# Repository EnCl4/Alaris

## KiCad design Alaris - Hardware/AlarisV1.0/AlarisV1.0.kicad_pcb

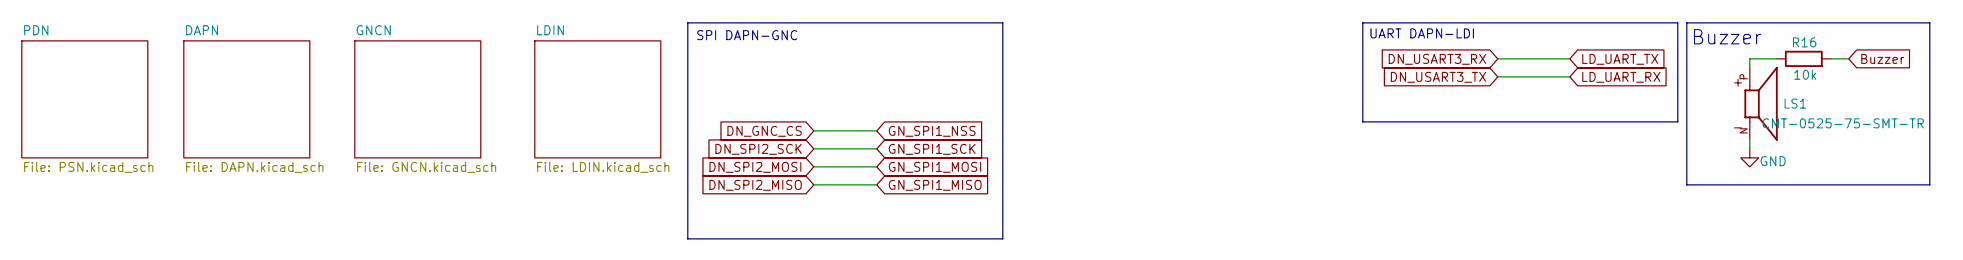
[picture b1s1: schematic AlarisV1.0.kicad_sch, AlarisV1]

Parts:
LS1: CMT-0525-75-SMT-TR; Buzzer5mm; PARTREV 1.0
R16: 10k; R_0603_1608Metric_Pad0.98x0.95mm_HandSolder

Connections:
Buzzer: R16.2; also elsewhere on the board
GND: LS1.N; also elsewhere on the board
unnamed: LS1.P, R16.1

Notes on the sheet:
Buzzer
SPI DAPN-GNC
UART DAPN-LDI

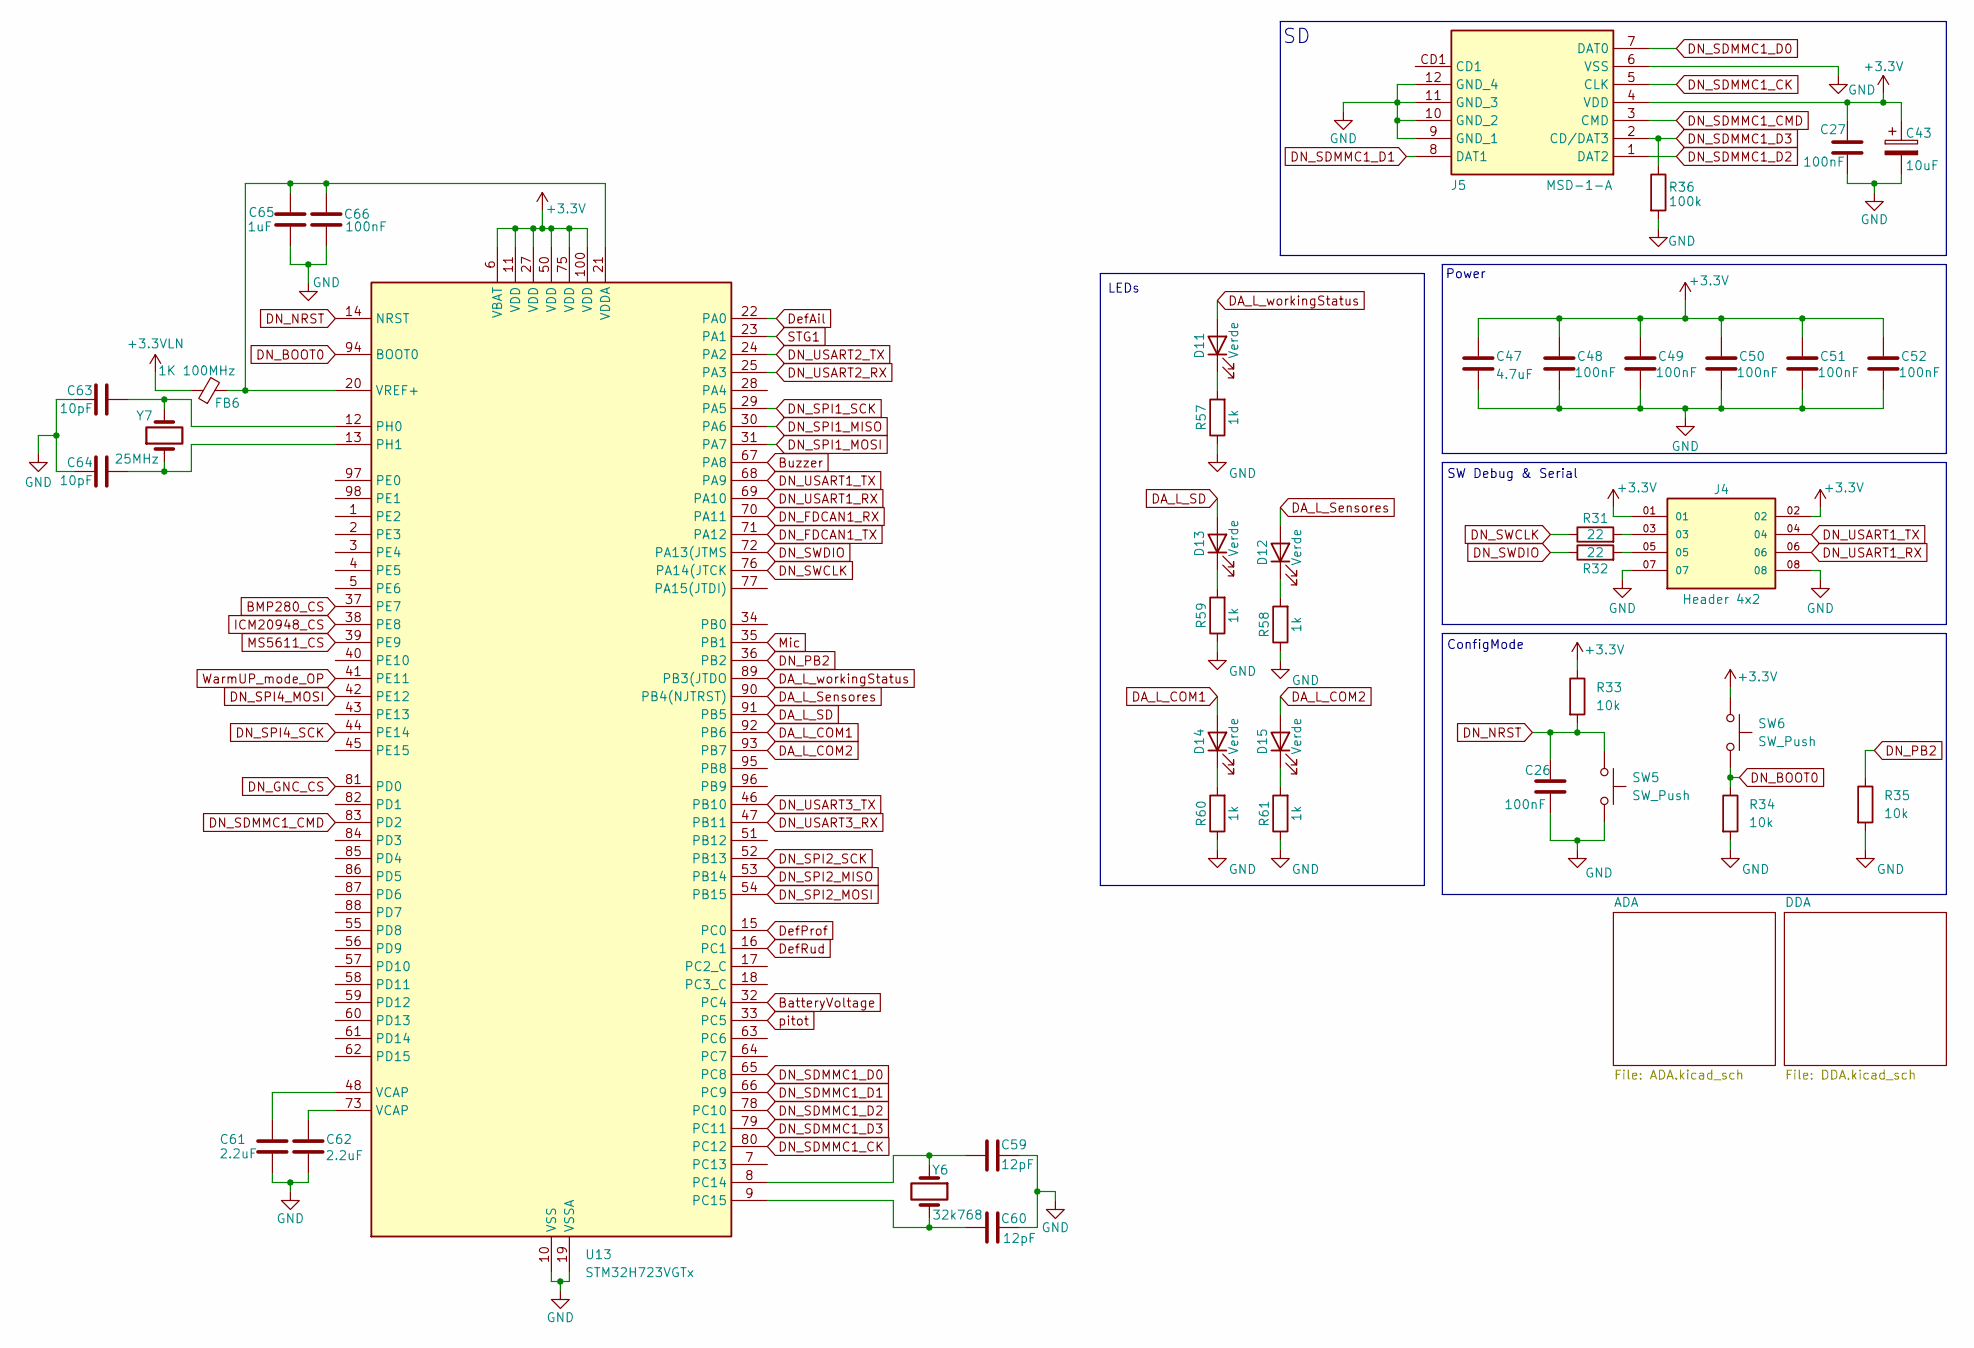
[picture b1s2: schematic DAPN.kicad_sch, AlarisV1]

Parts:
C26, C27, C48, C49, C50, C51, C52, C66: 100nF; C_0603_1608Metric_Pad1.08x0.95mm_HandSolder
C43: 10uF; CP_EIA-3216-18_Kemet-A_Pad1.58x1.35mm_HandSolder
C47: 4.7uF; C_0603_1608Metric_Pad1.08x0.95mm_HandSolder
C59, C60: 12pF; C_0603_1608Metric_Pad1.08x0.95mm_HandSolder
C61, C62: 2.2uF; C_0603_1608Metric_Pad1.08x0.95mm_HandSolder
C63, C64: 10pF; C_0603_1608Metric_Pad1.08x0.95mm_HandSolder
C65: 1uF; C_0603_1608Metric_Pad1.08x0.95mm_HandSolder
D11, D12, D13, D14, D15: Verde; LED_0603_1608Metric_Pad1.05x0.95mm_HandSolder
FB6: 1K 100MHz; C_0603_1608Metric_Pad1.08x0.95mm_HandSolder
J4: Header 4x2; Header4x2; PARTREV R
J5: MSD-1-A; MSD1A; Mouser Part Number 179-MSD-1-A
R31, R32: 22; R_0603_1608Metric_Pad0.98x0.95mm_HandSolder
R33, R34, R35: 10k; R_0603_1608Metric_Pad0.98x0.95mm_HandSolder
R36: 100k; R_0603_1608Metric_Pad0.98x0.95mm_HandSolder
R57, R58, R59, R60, R61: 1k; R_0603_1608Metric_Pad0.98x0.95mm_HandSolder
SW5, SW6: SW_Push; SKRK
U13: STM32H723VGTx; LQFP-100_14x14mm_P0.5mm
Y6: 32k768; Crystal_SMD_3215-2Pin_3.2x1.5mm
Y7: 25MHz; Crystal_SMD_3225-4Pin_3.2x2.5mm

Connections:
+3.3V: C27.1, C43.1, C47.1, C48.1, C49.1, C50.1, C51.1, C52.1, J4.01, J4.02, J5.4 (VDD), R33.1, SW6.1, U13.6 (VBAT), U13.11 (VDD), U13.27 (VDD), U13.50 (VDD), U13.75 (VDD), U13.100 (VDD); also elsewhere on the board
+3.3VLN: FB6.1; also elsewhere on the board
BMP280_CS: U13.37 (PE7); also elsewhere on the board
BatteryVoltage: U13.32 (PC4); also elsewhere on the board
Buzzer: U13.67 (PA8); also elsewhere on the board
DA_L_COM1: D14.2 (A), U13.92 (PB6)
DA_L_COM2: D15.2 (A), U13.93 (PB7)
DA_L_SD: D13.2 (A), U13.91 (PB5)
DA_L_Sensores: D12.2 (A), U13.90 (PB4(NJTRST))
DA_L_workingStatus: D11.2 (A), U13.89 (PB3(JTDO)
DN_BOOT0: R34.1, SW6.2, U13.94 (BOOT0)
DN_FDCAN1_RX: U13.70 (PA11)
DN_FDCAN1_TX: U13.71 (PA12)
DN_NRST: C26.2, R33.2, SW5.1, U13.14 (NRST)
DN_PB2: R35.1, U13.36 (PB2)
DN_SDMMC1_CK: J5.5 (CLK), U13.80 (PC12)
DN_SDMMC1_CMD: J5.3 (CMD), U13.83 (PD2)
DN_SDMMC1_D0: J5.7 (DAT0), U13.65 (PC8)
DN_SDMMC1_D1: J5.8 (DAT1), U13.66 (PC9)
DN_SDMMC1_D2: J5.1 (DAT2), U13.78 (PC10)
DN_SDMMC1_D3: J5.2 (CD/DAT3), R36.1, U13.79 (PC11)
DN_SPI1_MISO: U13.30 (PA6); also elsewhere on the board
DN_SPI1_MOSI: U13.31 (PA7); also elsewhere on the board
DN_SPI1_SCK: U13.29 (PA5); also elsewhere on the board
DN_SPI4_MOSI: U13.42 (PE12)
DN_SPI4_SCK: U13.44 (PE14)
DN_SWCLK: R31.1, U13.76 (PA14(JTCK)
DN_SWDIO: R32.1, U13.72 (PA13(JTMS)
DN_USART1_RX: J4.06, U13.69 (PA10)
DN_USART1_TX: J4.04, U13.68 (PA9)
DN_USART2_RX: U13.25 (PA3); also elsewhere on the board
DN_USART2_TX: U13.24 (PA2); also elsewhere on the board
DefAil: U13.22 (PA0); also elsewhere on the board
DefProf: U13.15 (PC0); also elsewhere on the board
DefRud: U13.16 (PC1); also elsewhere on the board
GND: C26.1, C27.2, C43.2, C47.2, C48.2, C49.2, C50.2, C51.2, C52.2, C59.2, C60.2, C61.2, C62.2, C63.2, C64.2, C65.2, C66.2, J4.07, J4.08, J5.6 (VSS), J5.9 (GND_1), J5.10 (GND_2), J5.11 (GND_3), J5.12 (GND_4), R34.2, R35.2, R36.2, R57.1, R58.1, R59.1, R60.1, R61.1, SW5.2, U13.10 (VSS), U13.19 (VSSA), U13.26 (VSS), U13.49 (VSS), U13.74 (VSS), U13.99 (VSS); also elsewhere on the board
ICM20948_CS: U13.38 (PE8); also elsewhere on the board
MS5611_CS: U13.39 (PE9); also elsewhere on the board
Mic: U13.35 (PB1); also elsewhere on the board
unnamed: C61.1, U13.48 (VCAP)
unnamed: C62.1, U13.73 (VCAP)
unnamed: D11.1 (K), R57.2
unnamed: D12.1 (K), R58.2
unnamed: D13.1 (K), R59.2
unnamed: D14.1 (K), R60.2
unnamed: D15.1 (K), R61.2
unnamed: J4.03, R31.2
unnamed: J4.05, R32.2
unnamed: C59.1, U13.8 (PC14), Y6.1
unnamed: C60.1, U13.9 (PC15), Y6.2
unnamed: C63.1, U13.12 (PH0), Y7.2
unnamed: C64.1, U13.13 (PH1), Y7.1
unnamed: C65.1, C66.1, FB6.2, U13.20 (VREF+), U13.21 (VDDA)
STG1: U13.23 (PA1); also elsewhere on the board
WarmUP_mode_OP: U13.41 (PE11); also elsewhere on the board
pitot: U13.33 (PC5); also elsewhere on the board

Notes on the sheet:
ConfigMode
LEDs
Power
SW Debug & Serial

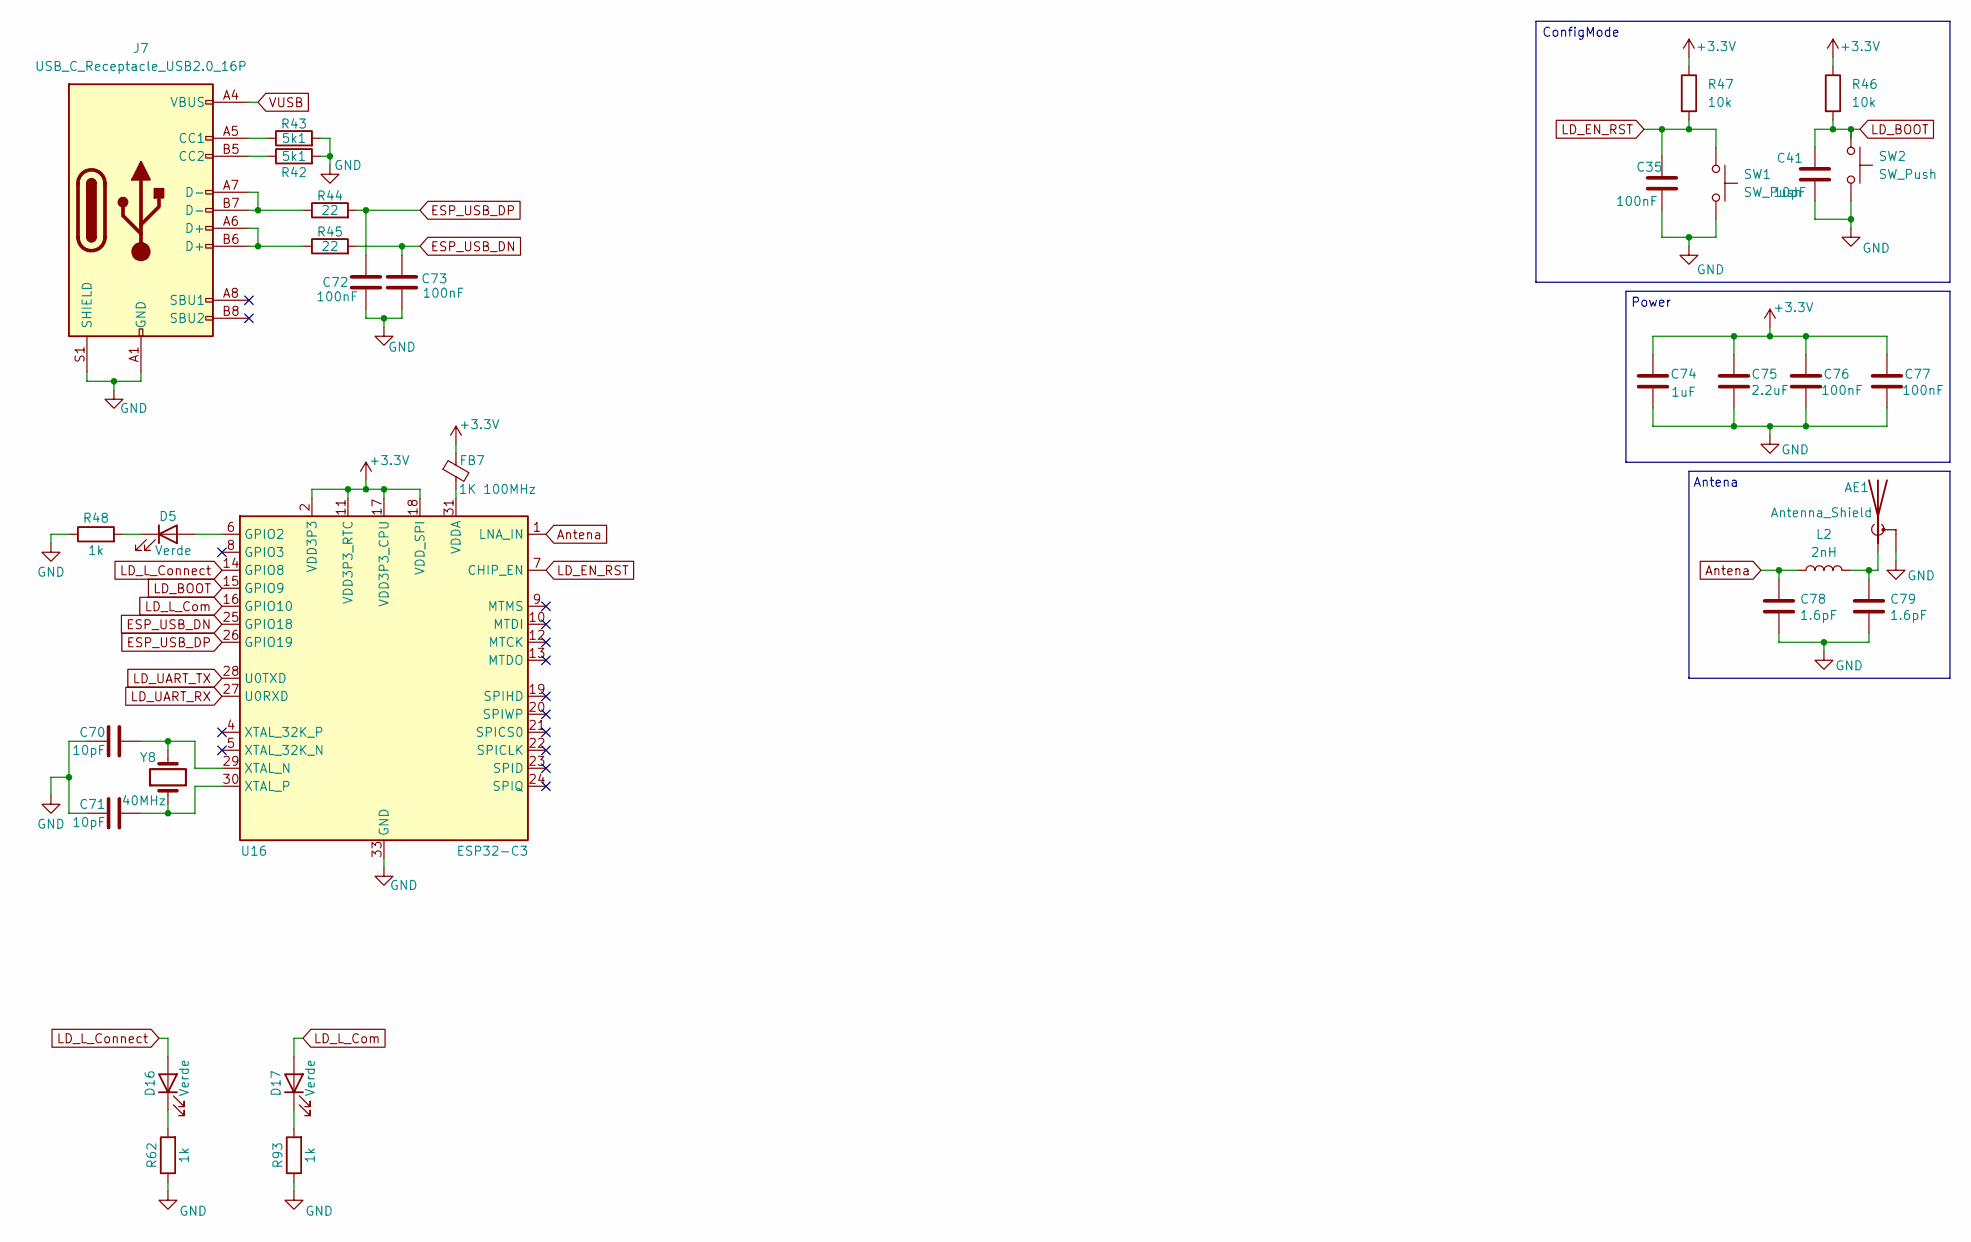
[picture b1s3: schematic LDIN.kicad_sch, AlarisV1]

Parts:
AE1: Antenna_Shield
C35, C72, C73, C76, C77: 100nF; C_0603_1608Metric_Pad1.08x0.95mm_HandSolder
C41, C70, C71: 10pF; C_0603_1608Metric_Pad1.08x0.95mm_HandSolder
C74: 1uF; C_0603_1608Metric_Pad1.08x0.95mm_HandSolder
C75: 2.2uF; C_0603_1608Metric_Pad1.08x0.95mm_HandSolder
C78, C79: 1.6pF; C_0603_1608Metric_Pad1.08x0.95mm_HandSolder
D5, D16, D17: Verde; LED_0603_1608Metric_Pad1.05x0.95mm_HandSolder
FB7: 1K 100MHz; C_0603_1608Metric_Pad1.08x0.95mm_HandSolder
J7: USB_C_Receptacle_USB2.0_16P; USB_C_Receptacle_G-Switch_GT-USB-7010ASV
L2: 2nH; L_0603_1608Metric_Pad1.05x0.95mm_HandSolder
R42, R43: 5k1; R_0603_1608Metric_Pad0.98x0.95mm_HandSolder
R44, R45: 22; R_0603_1608Metric_Pad0.98x0.95mm_HandSolder
R46, R47: 10k; R_0603_1608Metric_Pad0.98x0.95mm_HandSolder
R48, R62, R93: 1k; R_0603_1608Metric_Pad0.98x0.95mm_HandSolder
SW1, SW2: SW_Push; SKRK
U16: ESP32-C3; QFN-32-1EP_5x5mm_P0.5mm_EP3.7x3.7mm
Y8: 40MHz; Crystal_SMD_3225-4Pin_3.2x2.5mm

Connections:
+3.3V: C74.1, C75.1, C76.1, C77.1, FB7.1, R46.1, R47.1, U16.2 (VDD3P3), U16.3 (VDD3P3), U16.11 (VDD3P3_RTC), U16.17 (VDD3P3_CPU), U16.18 (VDD_SPI); also elsewhere on the board
Antena: C78.1, L2.1, U16.1 (LNA_IN)
ESP_USB_DN: C73.1, R45.2, U16.25 (GPIO18)
ESP_USB_DP: C72.1, R44.2, U16.26 (GPIO19)
GND: AE1.2 (Shield), C35.1, C41.1, C70.2, C71.2, C72.2, C73.2, C74.2, C75.2, C76.2, C77.2, C78.2, C79.2, J7.A1 (GND), J7.A12 (GND), J7.B1 (GND), J7.B12 (GND), J7.S1 (SHIELD), R42.2, R43.2, R48.1, R62.1, R93.1, SW1.2, SW2.2, U16.33 (GND); also elsewhere on the board
LD_BOOT: C41.2, R46.2, SW2.1, U16.15 (GPIO9)
LD_EN_RST: C35.2, R47.2, SW1.1, U16.7 (CHIP_EN)
LD_L_Com: D17.2 (A), U16.16 (GPIO10)
LD_L_Connect: D16.2 (A), U16.14 (GPIO8)
unnamed: AE1.1 (A), C79.1, L2.2
unnamed: D5.2 (A), U16.6 (GPIO2)
unnamed: D5.1 (K), R48.2
unnamed: D16.1 (K), R62.2
unnamed: D17.1 (K), R93.2
unnamed: FB7.2, U16.31 (VDDA), U16.32 (VDDA)
unnamed: J7.A5 (CC1), R43.1
unnamed: J7.B5 (CC2), R42.1
unnamed: J7.A6 (D+), J7.B6 (D+), R45.1
unnamed: J7.A7 (D-), J7.B7 (D-), R44.1
unnamed: C70.1, U16.29 (XTAL_N), Y8.2
unnamed: C71.1, U16.30 (XTAL_P), Y8.1
VUSB: J7.A4 (VBUS), J7.A9 (VBUS), J7.B4 (VBUS), J7.B9 (VBUS)

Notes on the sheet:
Power
Antena
ConfigMode

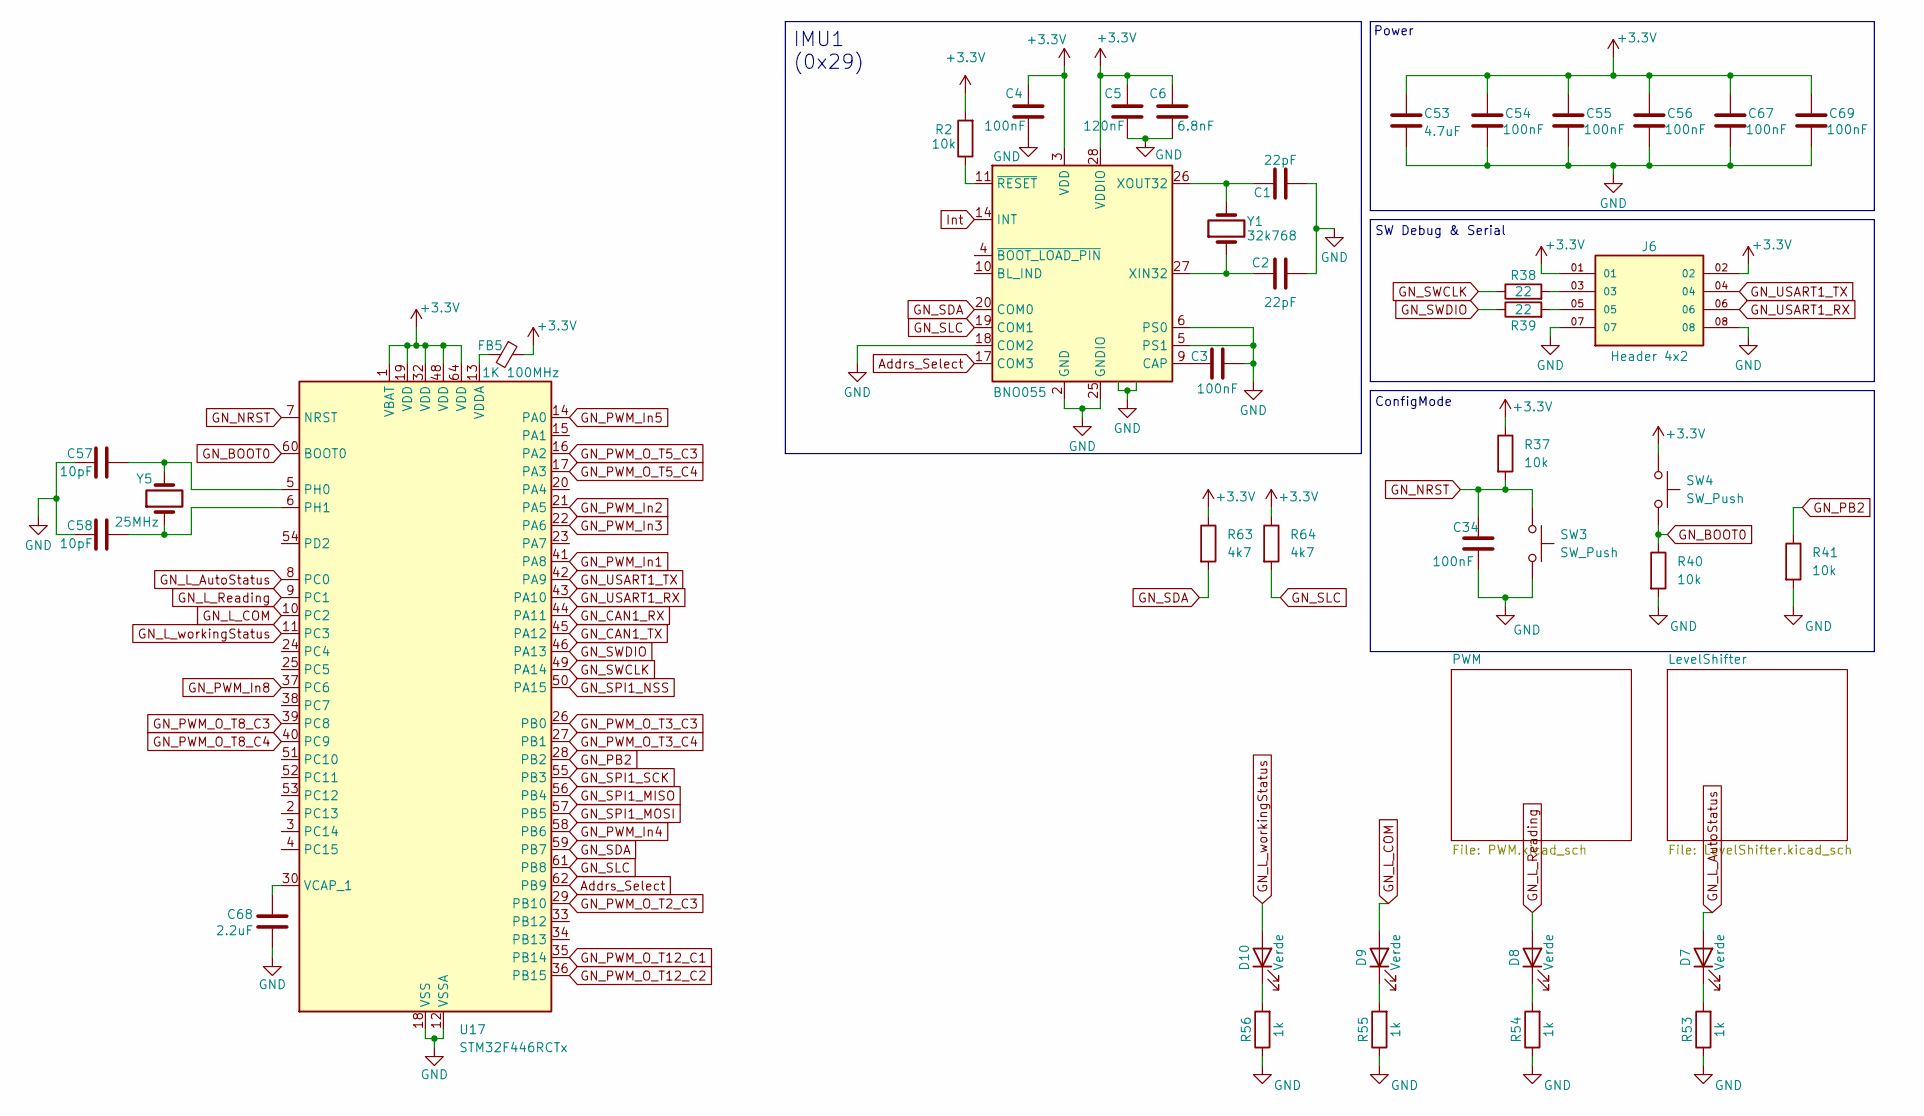
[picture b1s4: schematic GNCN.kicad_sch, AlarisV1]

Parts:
C1, C2: 22pF; C_0603_1608Metric_Pad1.08x0.95mm_HandSolder
C3, C4, C34, C54, C55, C56, C67, C69: 100nF; C_0603_1608Metric_Pad1.08x0.95mm_HandSolder
C5: 120nF; C_0603_1608Metric_Pad1.08x0.95mm_HandSolder
C6: 6.8nF; C_0603_1608Metric_Pad1.08x0.95mm_HandSolder
C53: 4.7uF; C_0603_1608Metric_Pad1.08x0.95mm_HandSolder
C57, C58: 10pF; C_0603_1608Metric_Pad1.08x0.95mm_HandSolder
C68: 2.2uF; C_0603_1608Metric_Pad1.08x0.95mm_HandSolder
D7, D8, D9, D10: Verde; LED_0603_1608Metric_Pad1.05x0.95mm_HandSolder
FB5: 1K 100MHz; C_0603_1608Metric_Pad1.08x0.95mm_HandSolder
J6: Header 4x2; Header4x2; PARTREV R
R2, R37, R40, R41: 10k; R_0603_1608Metric_Pad0.98x0.95mm_HandSolder
R38, R39: 22; R_0603_1608Metric_Pad0.98x0.95mm_HandSolder
R53, R54, R55, R56: 1k; R_0603_1608Metric_Pad0.98x0.95mm_HandSolder
R63, R64: 4k7; R_0603_1608Metric_Pad0.98x0.95mm_HandSolder
SW3, SW4: SW_Push; SKRK
U2: BNO055; LGA-28_5.2x3.8mm_P0.5mm
U17: STM32F446RCTx; LQFP-64_10x10mm_P0.5mm
Y1: 32k768; Crystal_SMD_3215-2Pin_3.2x1.5mm
Y5: 25MHz; Crystal_SMD_3225-4Pin_3.2x2.5mm

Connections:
+3.3V: C4.1, C5.1, C6.1, C53.1, C54.1, C55.1, C56.1, C67.1, C69.1, FB5.1, J6.01, J6.02, R2.2, R37.1, R63.1, R64.1, SW4.1, U2.3 (VDD), U2.28 (VDDIO), U17.1 (VBAT), U17.19 (VDD), U17.32 (VDD), U17.48 (VDD), U17.64 (VDD); also elsewhere on the board
Addrs_Select: U2.17 (COM3), U17.62 (PB9)
GND: C1.2, C2.2, C3.2, C4.2, C5.2, C6.2, C34.1, C53.2, C54.2, C55.2, C56.2, C57.2, C58.2, C67.2, C68.2, C69.2, J6.07, J6.08, R40.2, R41.2, R53.1, R54.1, R55.1, R56.1, SW3.2, U2.2 (GND), U2.5 (PS1), U2.6 (PS0), U2.15 (PIN15), U2.16 (PIN16), U2.18 (COM2), U2.25 (GNDIO), U17.12 (VSSA), U17.18 (VSS), U17.31 (VSS), U17.47 (VSS), U17.63 (VSS); also elsewhere on the board
GN_BOOT0: R40.1, SW4.2, U17.60 (BOOT0)
GN_CAN1_RX: U17.44 (PA11)
GN_CAN1_TX: U17.45 (PA12)
GN_L_AutoStatus: D7.2 (A), U17.8 (PC0)
GN_L_COM: D9.2 (A), U17.10 (PC2)
GN_L_Reading: D8.2 (A), U17.9 (PC1)
GN_L_workingStatus: D10.2 (A), U17.11 (PC3)
GN_NRST: C34.2, R37.2, SW3.1, U17.7 (NRST)
GN_PB2: R41.1, U17.28 (PB2)
GN_PWM_In1: U17.41 (PA8); also elsewhere on the board
GN_PWM_In2: U17.21 (PA5); also elsewhere on the board
GN_PWM_In3: U17.22 (PA6); also elsewhere on the board
GN_PWM_In4: U17.58 (PB6); also elsewhere on the board
GN_PWM_In5: U17.14 (PA0); also elsewhere on the board
GN_PWM_In8: U17.37 (PC6); also elsewhere on the board
GN_PWM_O_T2_C3: U17.29 (PB10); also elsewhere on the board
GN_PWM_O_T3_C3: U17.26 (PB0); also elsewhere on the board
GN_PWM_O_T3_C4: U17.27 (PB1); also elsewhere on the board
GN_PWM_O_T5_C3: U17.16 (PA2)
GN_PWM_O_T5_C4: U17.17 (PA3); also elsewhere on the board
GN_PWM_O_T8_C3: U17.39 (PC8); also elsewhere on the board
GN_PWM_O_T8_C4: U17.40 (PC9); also elsewhere on the board
GN_PWM_O_T12_C1: U17.35 (PB14); also elsewhere on the board
GN_PWM_O_T12_C2: U17.36 (PB15); also elsewhere on the board
GN_SDA: R63.2, U2.20 (COM0), U17.59 (PB7)
GN_SLC: R64.2, U2.19 (COM1), U17.61 (PB8)
GN_SWCLK: R38.1, U17.49 (PA14)
GN_SWDIO: R39.1, U17.46 (PA13)
GN_USART1_RX: J6.06, U17.43 (PA10)
GN_USART1_TX: J6.04, U17.42 (PA9)
Int: U2.14 (INT)
unnamed: D7.1 (K), R53.2
unnamed: D8.1 (K), R54.2
unnamed: D9.1 (K), R55.2
unnamed: D10.1 (K), R56.2
unnamed: J6.03, R38.2
unnamed: J6.05, R39.2
unnamed: C3.1, U2.9 (CAP)
unnamed: C2.1, U2.27 (XIN32), Y1.1
unnamed: C1.1, U2.26 (XOUT32), Y1.2
unnamed: R2.1, U2.11 (~RESET)
unnamed: C57.1, U17.5 (PH0), Y5.2
unnamed: C58.1, U17.6 (PH1), Y5.1
unnamed: C68.1, U17.30 (VCAP_1)
unnamed: FB5.2, U17.13 (VDDA)

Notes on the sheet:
SW Debug & Serial
Power
ConfigMode
IMU1 (0x29)

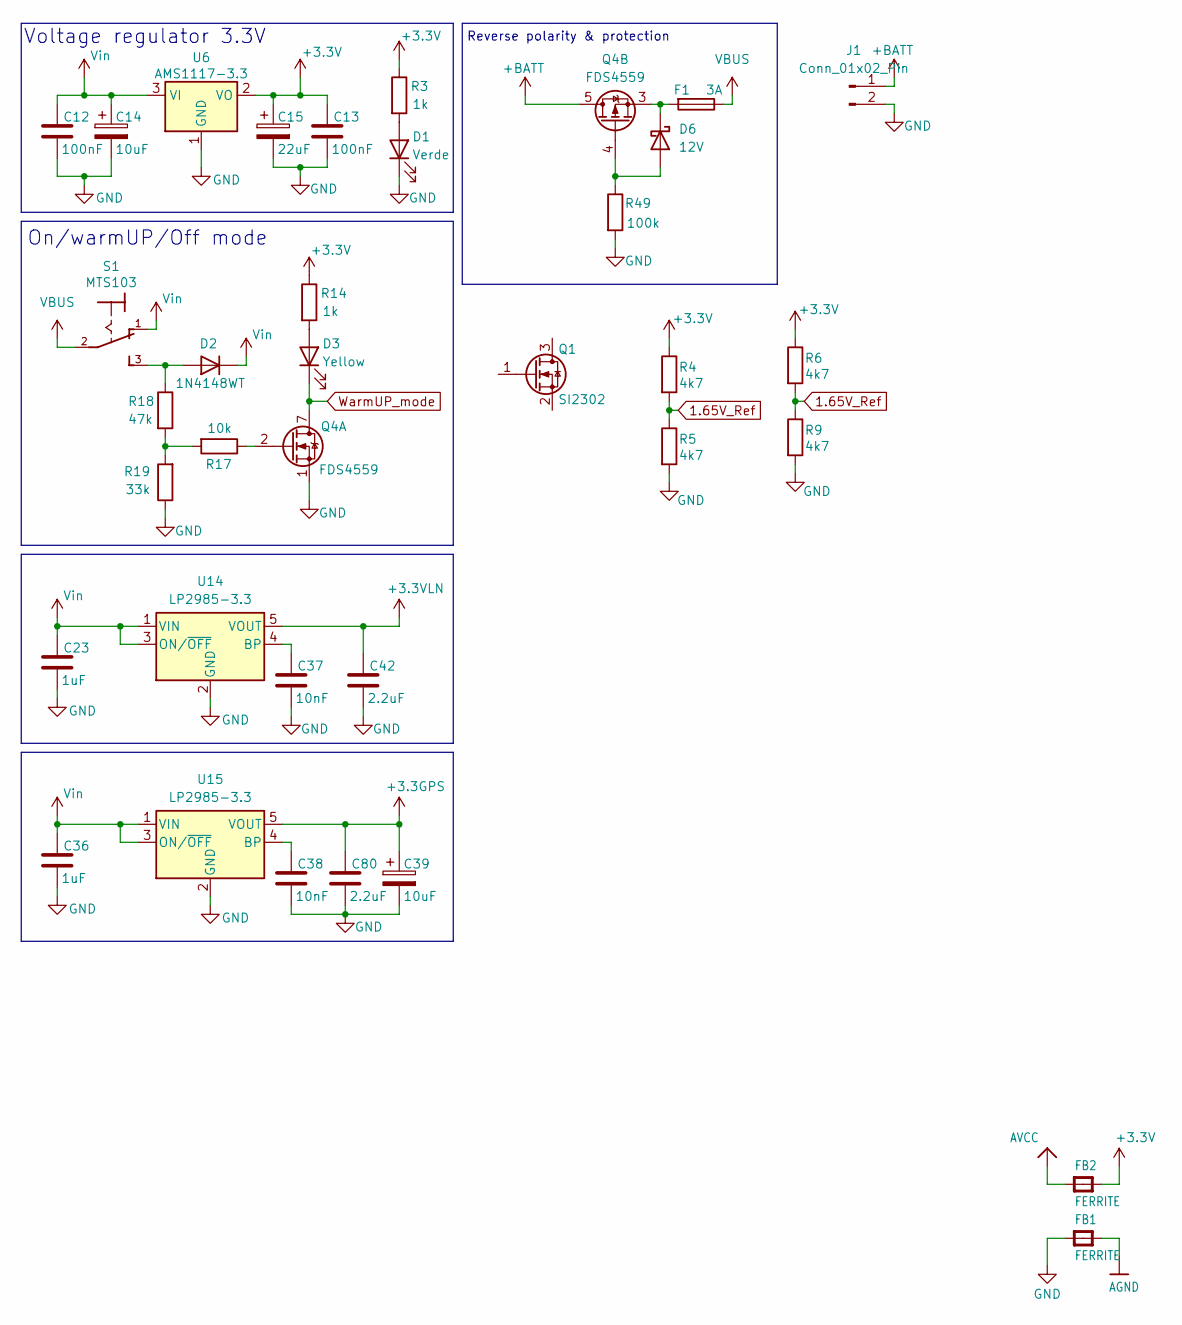
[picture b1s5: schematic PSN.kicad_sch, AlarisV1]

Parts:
C12, C13: 100nF; C_0603_1608Metric_Pad1.08x0.95mm_HandSolder
C14, C39: 10uF; CP_EIA-3216-18_Kemet-A_Pad1.58x1.35mm_HandSolder
C15: 22uF; CP_EIA-3216-18_Kemet-A_Pad1.58x1.35mm_HandSolder
C23, C36: 1uF; C_0603_1608Metric_Pad1.08x0.95mm_HandSolder
C37, C38: 10nF; C_0603_1608Metric_Pad1.08x0.95mm_HandSolder
C42, C80: 2.2uF; C_0603_1608Metric_Pad1.08x0.95mm_HandSolder
D1: Verde; LED_0603_1608Metric_Pad1.05x0.95mm_HandSolder
D2: 1N4148WT; D_SOD-523
D3: Yellow; LED_0603_1608Metric_Pad1.05x0.95mm_HandSolder
D6: 12V; D_0603_1608Metric_Pad1.05x0.95mm_HandSolder
F1: 3A; Fuse_0603_1608Metric_Pad1.05x0.95mm_HandSolder
FB1, FB2: FERRITE; C_0603_1608Metric_Pad1.08x0.95mm_HandSolder
J1: Conn_01x02_Pin; JST_EH_B2B-EH-A_1x02_P2.50mm_Vertical
Q1: SI2302
Q4: FDS4559; SOIC-8_3.9x4.9mm_P1.27mm
R3, R14: 1k; R_0603_1608Metric_Pad0.98x0.95mm_HandSolder
R4, R5, R6, R9: 4k7; R_0603_1608Metric_Pad0.98x0.95mm_HandSolder
R17: 10k; R_0603_1608Metric_Pad0.98x0.95mm_HandSolder
R18: 47k; R_0603_1608Metric_Pad0.98x0.95mm_HandSolder
R19: 33k; R_0603_1608Metric_Pad0.98x0.95mm_HandSolder
R49: 100k; R_0603_1608Metric_Pad0.98x0.95mm_HandSolder
S1: MTS103
U6: AMS1117-3.3; SOT-223-3_TabPin2
U14, U15: LP2985-3.3; SOT-23-5

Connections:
1.65V_Ref: R4.2, R5.1, R6.2, R9.1; also elsewhere on the board
+3.3GPS: C39.1, C80.1, U15.5 (VOUT); also elsewhere on the board
+3.3V: C13.1, C15.1, FB2.2, R3.1, R4.1, R6.1, R14.1, U6.2 (VO); also elsewhere on the board
+3.3VLN: C42.1, U14.5 (VOUT); also elsewhere on the board
+BATT: J1.1, Q4.5 (D), Q4.6 (D)
AGND: FB1.2; also elsewhere on the board
AVCC: FB2.1; also elsewhere on the board
GND: C12.2, C13.2, C14.2, C15.2, C23.2, C36.2, C37.2, C38.2, C39.2, C42.2, C80.2, D1.1 (K), FB1.1, J1.2, Q4.1 (S), R5.2, R9.2, R19.1, R49.2, U6.1 (GND), U14.2 (GND), U15.2 (GND); also elsewhere on the board
unnamed: D1.2 (A), R3.2
unnamed: D2.2 (A), R18.1, S1.3
unnamed: D3.2 (A), R14.2
unnamed: D6.2 (A), Q4.4 (G), R49.1
unnamed: D6.1 (K), F1.2, Q4.3 (1)
unnamed: Q4.2 (G), R17.1
unnamed: R17.2, R18.2, R19.2
unnamed: C37.1, U14.4 (BP)
unnamed: C38.1, U15.4 (BP)
VBUS: F1.1, S1.2
Vin: C12.1, C14.1, C23.1, C36.1, D2.1 (K), S1.1, U6.3 (VI), U14.1 (VIN), U14.3 (ON/~OFF), U15.1 (VIN), U15.3 (ON/~OFF); also elsewhere on the board
WarmUP_mode: D3.1 (K), Q4.7 (D), Q4.8 (D); also elsewhere on the board

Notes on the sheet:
Voltage regulator 3.3V
On/warmUP/Off mode
Reverse polarity & protection

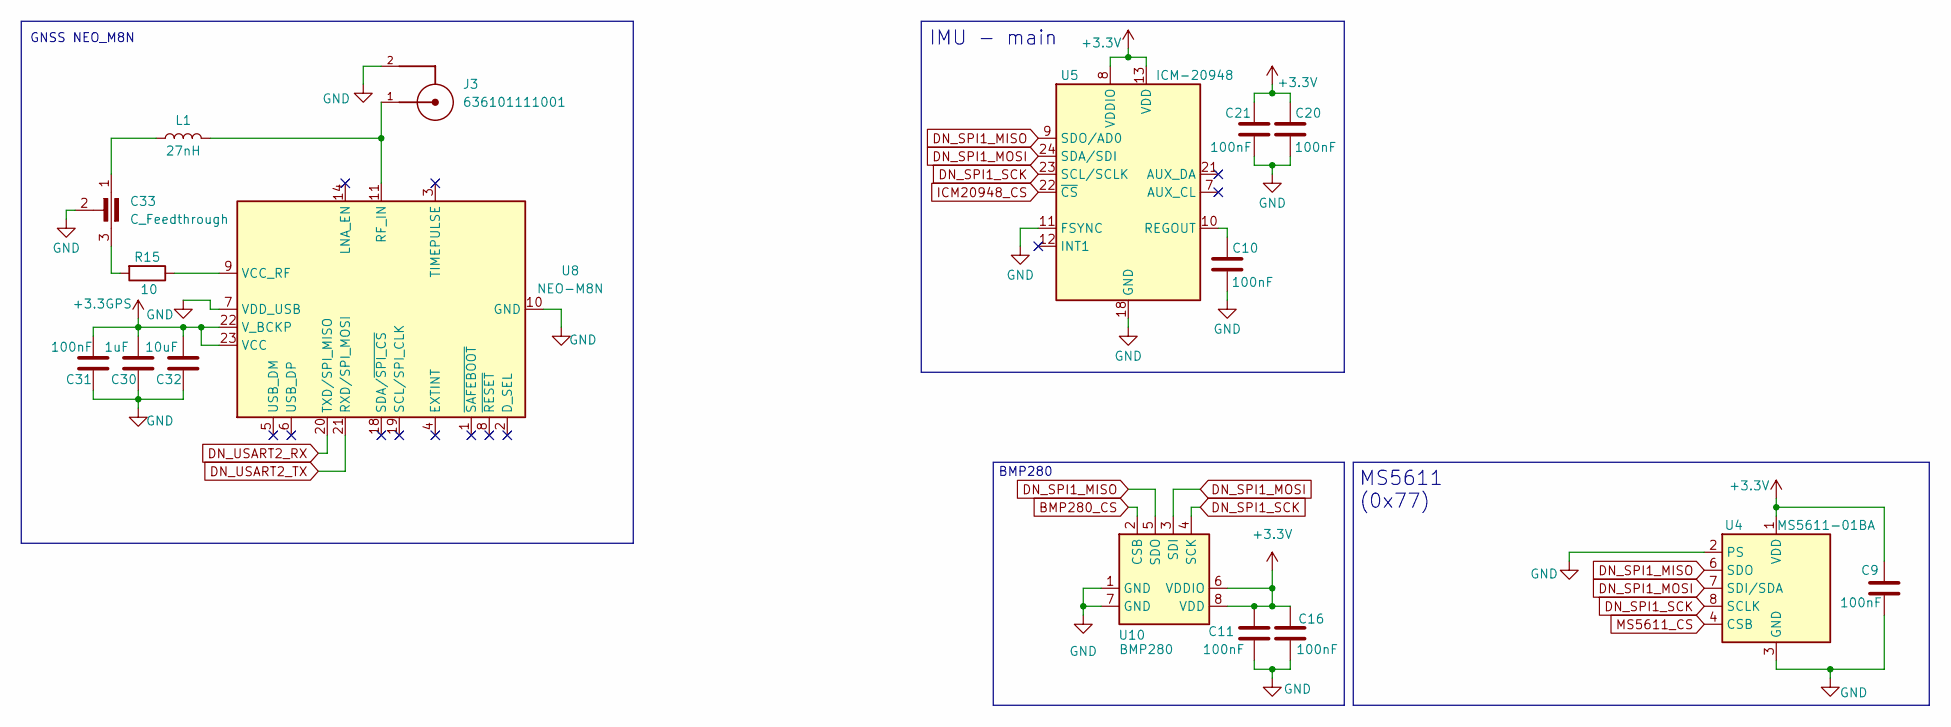
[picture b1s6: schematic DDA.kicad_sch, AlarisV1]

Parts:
C9, C10, C11, C16, C20, C21, C31: 100nF; C_0603_1608Metric_Pad1.08x0.95mm_HandSolder
C30: 1uF; C_0603_1608Metric_Pad1.08x0.95mm_HandSolder
C32: 10uF; C_0603_1608Metric_Pad1.08x0.95mm_HandSolder
C33: C_Feedthrough
J3: 636101111001
L1: 27nH; L_0603_1608Metric_Pad1.05x0.95mm_HandSolder
R15: 10; R_0603_1608Metric_Pad0.98x0.95mm_HandSolder
U4: MS5611-01BA; LGA-8_3x5mm_P1.25mm
U5: ICM-20948; InvenSense_QFN-24_3x3mm_P0.4mm
U8: NEO-M8N; ublox_NEO
U10: BMP280; Bosch_LGA-8_2x2.5mm_P0.65mm_ClockwisePinNumbering

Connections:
+3.3GPS: C30.2, C31.2, C32.2, U8.22 (V_BCKP), U8.23 (VCC); also elsewhere on the board
+3.3V: C9.1, C11.1, C16.1, C20.1, C21.2, U4.1 (VDD), U5.8 (VDDIO), U5.13 (VDD), U10.6 (VDDIO), U10.8 (VDD); also elsewhere on the board
BMP280_CS: U10.2 (CSB); also elsewhere on the board
DN_SPI1_MISO: U4.6 (SDO), U5.9 (SDO/AD0), U10.5 (SDO); also elsewhere on the board
DN_SPI1_MOSI: U4.7 (SDI/SDA), U5.24 (SDA/SDI), U10.3 (SDI); also elsewhere on the board
DN_SPI1_SCK: U4.8 (SCLK), U5.23 (SCL/SCLK), U10.4 (SCK); also elsewhere on the board
DN_USART2_RX: U8.20 (TXD/SPI_MISO); also elsewhere on the board
DN_USART2_TX: U8.21 (RXD/SPI_MOSI); also elsewhere on the board
GND: C9.2, C10.2, C11.2, C16.2, C20.2, C21.1, C30.1, C31.1, C32.1, C33.2, J3.2, J3.3, U4.2 (PS), U4.3 (GND), U5.11 (FSYNC), U5.18 (GND), U5.20 (GND), U8.7 (VDD_USB), U8.10 (GND), U8.12 (GND), U8.13 (GND), U8.24 (GND), U10.1 (GND), U10.7 (GND); also elsewhere on the board
ICM20948_CS: U5.22 (~CS); also elsewhere on the board
MS5611_CS: U4.4 (CSB), U4.5 (CSB); also elsewhere on the board
unnamed: C33.1, L1.1
unnamed: C33.3, R15.2
unnamed: C10.1, U5.10 (REGOUT)
unnamed: J3.1, L1.2, U8.11 (RF_IN)
unnamed: R15.1, U8.9 (VCC_RF)

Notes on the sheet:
BMP280
MS5611 (0x77)
GNSS NEO_M8N
IMU - main
